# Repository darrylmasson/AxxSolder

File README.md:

Note - this is a fork of AxxSolder that replaces the MCU with the RP2040 because I felt like it. Major portions of this README will be rewritten at some point.

# AxxSolder Overview
AxxSolder is a STM32 based soldering iron controller for JBC C115, C210 and C245 cartridges. 
Two different versions are designed around the same PCB and software - one soldering station based on the [JBC ADS stand](https://www.jbctools.com/ad-sf-stand-for-t210-t245-handles-product-2018.html) and one portable version. The hardware takes a USB-C Power Delivery source. If a 65W, 20V USB-PD supply is used then NT115 and T210 handles can be powered at full power and T245 at limited power. The software is written for the RP2040 and implements a PID for temperature control, TFT display driver, sleep function when the handle is at rest and functions for read/write user settings to flash. Enclosures for both station and portable versions are 3D printed and design files are available under [/CAD](https://github.com/AxxAxx/AxxSolder/tree/main/CAD). A video showing the AxxSolder station can be found under [DEMO](#demo). A *bill of materials* (BOM) with individual component prices can be found under [/bom](https://github.com/AxxAxx/AxxSolder/tree/main/AxxSolder_hardware/bom).  

# Questions and support
Please use [Discord](https://discord.gg/dRD2ZfmyHY) for build related and general questions.

# Table of Contents
- [AxxSolder Overview](#axxsolder-overview)
- [Questions and support](#questions-and-support)
- [Features](#features)
- [Cartridge differences](#cartridge-differences)
- [Schematic](#schematic)
- [PCB](#pcb)
- [Software Version History and Hardware Compatibility](#software-version-history-and-hardware-compatibility)
- [DEMO](#demo)
- [AxxSolder Station](#axxsolder-station)
- [AxxSolder Portable](#axxsolder-portable)
- [Recommended power supply](#recommended-power-supply)
- [Handle identification and connections](#handle-identification-and-connections)
- [Firmware update](#firmware-update)
- [First start up after build](#first-start-up-after-build)
- [Settings](#settings)
- [PID control](#pid-control)
- [Temperature calibration](#temperature-calibration)
- [Temperature measurement](#temperature-measurement)

# Features
- The tip temperature is set by a rotary encoder. Pressing the encoder puts AxxSolder into Sleep mode and heating is turned off, press again to wake up.  
- AxxSolder is capable of driving C115, C210 and C245 style cartridges from JBC. With the "H_sense1" and "H_sense2" inputs AxxSolder can determine if the connected handle is either a NT115, T210 or T245 and adjust max output power accordingly. The max power output is limited in software to 120W for T245, 60W for T210 and 20W for NT115 handles.
- When the handle is put into the stand (connected to Stand_sense) AxxSolder goes into "Standby mode". On the portable version an aluminium plate is mounted and allows the AxxSolder to go into Standby mode when the cartridge or handle rests against it. After 10 min in Standby mode AxxSolder goes into "Sleep mode" and turns heating completely off. This is similar to what JBC calls [Sleep and Hibernation](https://www.jbctools.com/intelligent-heat-management.html).  
- If AxxSolder is left in normal running mode for longer than 30 min, the station automatically goes into sleep mode after 30 min as a safety feature.  
- Should the temperature ever go higher than 480 deg C overheating is detected and the station goes into sleep mode in order to protect the tip.
- User settings are stored in non volatile flash and can be configured via a settings menu described in [SETTINGS](#settings).
- The two buttons are used to store temperature presets, e.g. 330 deg C and 430 deg C. Both preset temperatures are configurable in the settings menu.
- The TFT display used in this project is a 2 inch 320x240 Color TFT display [2.0" 320x240 Color IPS TFT Display](https://www.adafruit.com/product/4311) and shows information about:
  - Set temperature
  - Actual temperature
  - Current power as a bar graph
  - In case of sleep mode, the power bar shows "ZzZzZz"
  - In case of Standby mode, the power bar shows "STANDBY"
  - Input voltage
  - MCU temperature
  - Current detected handle type

# Cartridge differences
Cartridges from JBC do all contain a thermocouple element to read the tip temperature and a resistive heater element. The configuration of thermocouple and heater element differ slightly between cartridge models. In order to determine the internal configuration of the cartridges two cross sections were done. These show clearly how the C210 and C245 cartridges are constructed internally. The images can be seen here: [https://www.eevblog.com/forum/projects/axxsolder-jbc-soldering-controller](https://www.eevblog.com/forum/projects/axxsolder-jbc-soldering-controller/msg5124267/#msg5124267).
As the thermocouple output also differs (see my measurements [Temperature calibration](#temperature-calibration)) the correct handle/cartridge type has to be set. This is done automatically be the inputs "Handle_sense_1" and "Handle_sense_2" This can be done thanks to the design of the handle connector. For the JCB T210 handle pin 5 and 6 are connected internally in the connector and for NT115 pin 3 and 5 should be connected. This allows AxxSolder to sense which handle is connected and assign correct thermocouple correction, PID parameters and max output power.

# Schematic
The schematic for AxxSolder is shown below. Both station and portable versions use the same PCB and software. The MCU is a [STM32G431CBT6](https://www.st.com/en/microcontrollers-microprocessors/stm32g431cb.html). 

# PCB
The PCBs are designed in KiCad and manufactured by [PCBWay](https://www.pcbway.com/). PCBWay has sponsored this project with PCBs and stencils. As usual the quality of the PCBs is great. As some components have a rather fine pitch (0,5 mm as of the LQFP-48 package of the STM32) and some packages are "no lead" with a bottom thermal pad e.g. the WSON-8 package of the OPA2387 it is suggested to use a stencil to apply solder paste and then reflow the board using either a reflow oven or hot-plate. The boards on the image below were reflowed on a hot-plate (a homemade AxxPlate). A microscope is also recommended and helpful during assembly.
Printed Circuit Boards with assembled components are shown in the image below.

A 3D view (from and back) of the AxxSolder PCB is generated with KiCad and shown below. 

# Software Version History and Hardware Compatibility
| Version | Date  | Hardware Compatibility |
|---------|------|----------------------|
|[v3.0.2](https://github.com/AxxAxx/AxxSolder/releases/tag/v3.0.1)|Apr 25, 2024|V3.*|
|[v3.0.1](https://github.com/AxxAxx/AxxSolder/releases/tag/v3.0.1)|Mar 26, 2024|V3.*|
|[v3.0.0](https://github.com/AxxAxx/AxxSolder/releases/tag/v3.0.0)|Mar 02, 2024|V3.*|
|[v2.2.4](https://github.com/AxxAxx/AxxSolder/releases/tag/v2.2.2)|Dec 11, 2023|V2.*|
|[v2.2.4](https://github.com/AxxAxx/AxxSolder/releases/tag/v2.2.2)|Nov 28, 2023|V2.*|
|[v2.2.3](https://github.com/AxxAxx/AxxSolder/releases/tag/v2.2.2)|Nov 25, 2023|V2.*|
|[v2.2.2](https://github.com/AxxAxx/AxxSolder/releases/tag/v2.2.2)|Oct 24, 2023|V2.*|
|[v2.2.0](https://github.com/AxxAxx/AxxSolder/releases/tag/v2.2.0)|Oct 20, 2023|V2.*|
|[v2.1.3-revC](https://github.com/AxxAxx/AxxSolder/releases/tag/v2.1.3-revC)|Oct 16, 2023|V2.*|
|[v2.1.1](https://github.com/AxxAxx/AxxSolder/releases/tag/v2.1.1)|Oct 7, 2023|V2.*|
|[v2.1.0](https://github.com/AxxAxx/AxxSolder/releases/tag/v2.1.0)|Oct 7, 2023|V2.*|

# DEMO
(This shows AxxSolder 2 and not the latest AxxSolder 3)  
Click on the gif to get to YouTube and see the demo in full resolution.  

# AxxSolder Station
The preferred setup is to pair AxxSolder with the [JBC ADS stand](https://www.jbctools.com/ad-sf-stand-for-t210-t245-handles-product-2018.html). This makes a very nice, compact and powerful soldering station. The JBC ADS stand is paired with a custom 3D printed enclosure for AxxSolder and the PCB is mounted with two mounting brackets. All 3D printed parts are available under [/CAD](https://github.com/AxxAxx/AxxSolder/tree/main/CAD). 
  
The JBC ADS stand comes with a silicone cable fitted with two Binder 99-0621-00-07 connectors. In order to use this cable a Binder 99-0624-00-07 is mounted into the AxxSolder enclosure and wired as the image below:  
  
By default, the stand separates the two signals coming from the "tool rest position" and the "tip change position" and does NOT have two separate connections for tip sensing 1 and 2 (as is needed). Therefore, a modification is done to the PCB inside the JBC ADS stand in order to combine the "tool rest position" and the "tip change position" sense into one connection and separate the two tip sense connections. This is shown in the image above. The stand is held together with two PH0 screws from the side. 

# AxxSolder Portable
It is often nice to have a compact and portable soldering iron controller for when you are away from your comfortable desk. A neat powerful package with the same capabilities as your main soldering station. This is why AxxSolder Portable was designed. The only difference between AxxSolder station and Portable is the enclosure. As AxxSolder accepts an input of 9-24 V it is compatible with a range of battery options. The author usually use a battery pack consisting of 12 Samsung INR18650 35E in a 3S4P configuration which works very well. The portable version has an aluminium tab on the enclosure connected to the same input on the PCB as the "handle rest" on the station version. This allows the user to rest the iron onto the aluminium tab and automatically enter sleep mode.   

The connections from the handle to the PCB through the Hirose RPC1-12RB-6P(71) connector is shown below. The blue wire in the portable version is connected to the aluminium plate which tells the AxxSolder to go into sleep mode when in contact with the soldering iron. The yellow wire is connected to pin 6 and is used to determine which handle is connected.

# Recommended power supply
A well-suited power supply with isolated output (SELV) is the Meanwell LRS-150-24. It is rated for 156 W at 24 V. A cover protecting the terminals for this power supply can be found under [/CAD](https://github.com/AxxAxx/AxxSolder/tree/main/CAD).  

# Handle identification and connections
In order for AxxSolder to know which type of handle (NT115, T210, T245) is connected specific pins must be connected within the handle connector. By default, the original JBC handle T245 has NO pins connected while in the original T210 pins 5 and 6 are connected. The original NT115 handle has a different connector from JBC and must be modified. If the user changes the connector or uses a non-genuine handle it is important to make sure that pin 5 and 3 is connected within the connector. All the necessary connections are shown in the image below. While powering on AxxSolder fir the first time after doing these connections within the handle connector or connections to AxxSolder it is wise to attach a handle without its cartridge and ensure that AxxSolder shows the correct handle type on the display. Failing to detect the handle type will cause damage to the tip as the thermal calibration and max power allowed will be wrong.  

# Firmware update
Programming or updating the firmware the STM32 MCU can be done in two ways, by using a SWD programmer or directly via USB. 
## SWD programmer
These come in a variety of models and are available from several different places online. In the below example a [STLINK-V3MINIE](https://www.st.com/en/development-tools/stlink-v3minie.html) SWD programmer is used. The MCU is programmed by the following steps:
1. Disconnect any soldering iron handles from AxxSolder during the firmware update process.
2. Download the latest AxxSolder.bin file from [Releases](https://github.com/AxxAxx/AxxSolder/releases)
3. Connect your SWD programmer to the target MCU with GND, 3.3V, (N)RST, SWCLK, SWDIO
4. If your SWD programmer *can not* supply 3.3V it is necessary to power the AxxSolder from an external supply.
5. Start your programming software. [STM32CubeProgrammer](https://www.st.com/en/development-tools/stm32cubeprog.html) is used in this example.
6. Connect to the target by selecting *ST-LINK* and click on *Connect*
7. Load the latest AxxSolder.bin downloaded in *Step 2* by clicking *Open file* and select the downloaded binary file.
8. Write the firmware to the MCU by clicking *Download*.
9. If you get the message *File download complete* everything succeeded and the SWD programmer can be disconnected and AxxSolder power cycled once and AxxSolder should boot.

## USB (DFU mode)
1. Disconnect any soldering iron handles from AxxSolder during the firmware update process.
2. Download the latest AxxSolder.bin file from [Releases](https://github.com/AxxAxx/AxxSolder/releases)
3. Connect AxxSolder via USB to a computer that runs [STM32CubeProgrammer](https://www.st.com/en/development-tools/stm32cubeprog.html).
4. Hold down the most right button while powering on AxxSolder to enter DFU mode.
5. Connect to the target by selecting *USB* and click on *Connect*
6. Load the latest AxxSolder.bin downloaded in *Step 2* by clicking *Open file* and select the downloaded binary file.
7. Write the firmware to the MCU by clicking *Download*.
8. If you get the message *File download complete* everything succeeded and the USB cable can be disconnected.
9. Power cycle once and AxxSolder should boot.

# First start up after build
The first start up after you have built your AxxSolder can be intense. Double check all solder connections under a loupe/microscope. Especially the OPA2387, LTC4440 and the STM32G431 are small packages with tight pad spacing and can have solder bridges. Do also double check the connections to the soldering iron/stand which are shown in this document under [AxxSolder Station](#axxsolder-station) and [AxxSolder Portable](#axxsolder-portable).  
The first thing to do after you have double-checked everything is to follow the steps under [Firmware update](#firmware-update). It is wise to do the first programming of AxxSolder without any handle piece and with only 3.3 V, not VDD. After the programming is done you can now power up AxxSolder again via either with 3.3 V, this time you can attach your handle. This allows you to test that your handle type is detected correctly (the detected handle type NT115/T210/T245 is shown in the display). The Standby feature can also be tested by touching the stand (STAND Input).  
If the handle is detected correctly, the Standby function works and the display works you proceed to test the 7.35V DC/DC. This is done by once again disconnect the handle, but this time apply current limited 9-24 V VDD. 100 mA at 24 V is enough to check that the display starts and that you can measure the 3 bus voltages; 3.3V, 7.35V and VDD. If the bus voltages look good and the display shows the main screen you are ready to apply full VDD power and attach the soldering handle.  
If you are not 110% sure about your soldering/connections it is wise to be on the safe side and keep your soldering tip in a water bath in over to prevent it from over-heating in an uncontrolled manner. During the development this method was used and saved a few of those expensive JBC cartridges..

# Settings
To access the user settings the user holds down the encoder button at start-up. A SETTINGS text is then presented and the button can be released. While in the settings there are several parameters available.
| Setting | Desciption  | Unit | Default |
|---------|------|----------------------|----------------------|
|Startup Temp|Default temperature selected after boot|deg C|330|
|Temp Offset|Temperature offset applied to measured temperature|deg C|0|
|Standby Temp|Temperature to go to after handle is set in stand|deg C|150|
|Standby Time|Time for which standby temperature is held before cooling down|minutes|10|
|Sleep Time|Time that the iron can be ON before cooling down (safety feature)|minutes|30|
|Buzzer Enable|Enable or Disable the buzzer|ON/OFF|ON|
|Preset Temp 1|Preset temperature for button 1|deg C|330|
|Preset Temp 2|Preset temperature for button 2|deg C|430|
|GPIO4 ON at run|Enable 3.3V output on GPIO4 when the iron is in run mode|ON/OFF|OFF|
|Screen rotation|Rotate the screen|"0"=-180 deg, "1"=-90 deg, "2"=0 deg, "3"=90 deg|2|
|Limit Power|Limit the output power|"0"=no user limit, "1"=10 W, "2"= 20 W, "3"= 30 W ...|0|
|-Load Default-|Load default parameters|N/A|N/A|
|-Save and Reboot-|Exit and Save|N/A|N/A|
|-Exit no Save-|Exit without Save|N/A|N/A|

# PID control
As the thermal mass of each cartridge differs the PID parameters should in theory be adjusted to each different cartridge. As a matter of simplification, the PID parameters are only different between the different handle types, NT115, T210 and T245. This gives a good enough PID performance in my tests. The Max allowed power is also different between handle types.
```c
	/* Determine if NT115 handle is detected */
	if((sensor_values.handle1_sense >= 0.5) && (sensor_values.handle2_sense < 0.5)){
		handle = NT115;
		sensor_values.max_power_watt = 20; //20W
		Kp = 3;
		Ki = 1;
		Kd = 0.25;
		PID_MAX_I_LIMIT = 100;
	}
	/* Determine if T210 handle is detected */
	else if((sensor_values.handle1_sense < 0.5) && (sensor_values.handle2_sense >= 0.5)){
		handle = T210;
		sensor_values.max_power_watt = 60; //60W
		Kp = 5;
		Ki = 5;
		Kd = 0.5;
		PID_MAX_I_LIMIT = 125;
	}
	else{
		handle = T245;
		sensor_values.max_power_watt = 120; //120W
		Kp = 8;
		Ki = 3;
		Kd = 0.5;
		PID_MAX_I_LIMIT = 150;
	}
	PID_SetTunings(&TPID, Kp, Ki, Kd); // Update PID parameters based on handle type
	PID_SetILimits(&TPID, -PID_MAX_I_LIMIT, PID_MAX_I_LIMIT); 	// Set max and min I limit
```
The PID parameters are adjusted to achieve a fast response with minimum overshoot and oscillation. The below image is showing the set temperature, actual temperature response as well as the P, I and D contributions during a heat-up cycle from 25 deg C to 330 deg C. This heat-up sequence takes ~1.5 seconds for a C210-007 cartridge.  

# Temperature calibration
The voltage from the thermocouple embedded inside the cartridge is amplified by an OPA2387 operational amplifier and then read by the ADC of the MCU. To correlate the measured ADC value to the cartridge temperature experiments were done. A constant power was applied to the heating element of the cartridge and the ADC value was read as well as the actual tip temperature. The tip temperature was measured by a "Soldering Tip Thermocouple" used in e.g. the Hakko FG-100.   
The measured data was recorded and plotted for both the C115, C210 and C245 cartridges. The specific cartridges used were the C115112, C210-007 and C245-945. The measured data were fitted to polynomial equations:  
$Temp_{C115}[deg] =  5.10e^{-5} * ADC^2 + 0.42* ADC + 20.15$  
$Temp_{C210}[deg] =  4.22e^{-6} * ADC^2 + 0.32* ADC + 20.97$  
$Temp_{C245}[deg] = -4.73e^{-7} * ADC^2 + 0.12* ADC + 23.78$  
These are then used in the software to retrieve correct tip temperatures.

# Temperature measurement
As the thermocouple and heater element is connected in series inside the JBC cartridges and the thermocouple voltage measures over the same pins as the heating element we have to be careful when to do the temperature measurement. In order to not disturb the thermocouple measurement with heater element switching, the switching is turned off for 0.5 ms just before the temperature measurement is taken. The 0.5 ms delay ensures that the switching is turned off and the thermocouple signal is stabilized around a stable voltage.  
The measured signal over the thermocouple is clamped to 3.3V with a BAV199 Schottky diode in order to protect the op-amp OPA2387. The voltage measurement is taken by the internal ADC in DMA mode with a circular buffer. The buffer holds several measurements which are averaged and filtered in software.  
The yellow curve in the image below (Channel 1) shows the PWM signal driving the gate of the MOSFET. The green curve shows the amplified voltage between GREEN and RED wire in the JBC handle for at 330 degree C and 5% power and the purple 25 degree C and at 80% power (the tip held under water trying to heat up).
The blue pulse indicates the wait time of 0.5 ms and the purple pulse is where the ADC is sampled.

# Current measurement
The current is sampled four times per second by a 30 us current pulse through the heater. This is done both to check if there is a functioning tip in the handle (otherwise the display shows "---" at current temp) and to be able to calculate the power drawn by the heater. By knowing how much the heater draws in ampere the actual power can be calculated by knowing the bus voltage and pulse duty cycle. to measure the current the gate to the MOSFET is turned on, 10 us later the voltage over the current shunt is sampled by the ADC and the result is converted. This is shown the image below.

## Stargazers over time

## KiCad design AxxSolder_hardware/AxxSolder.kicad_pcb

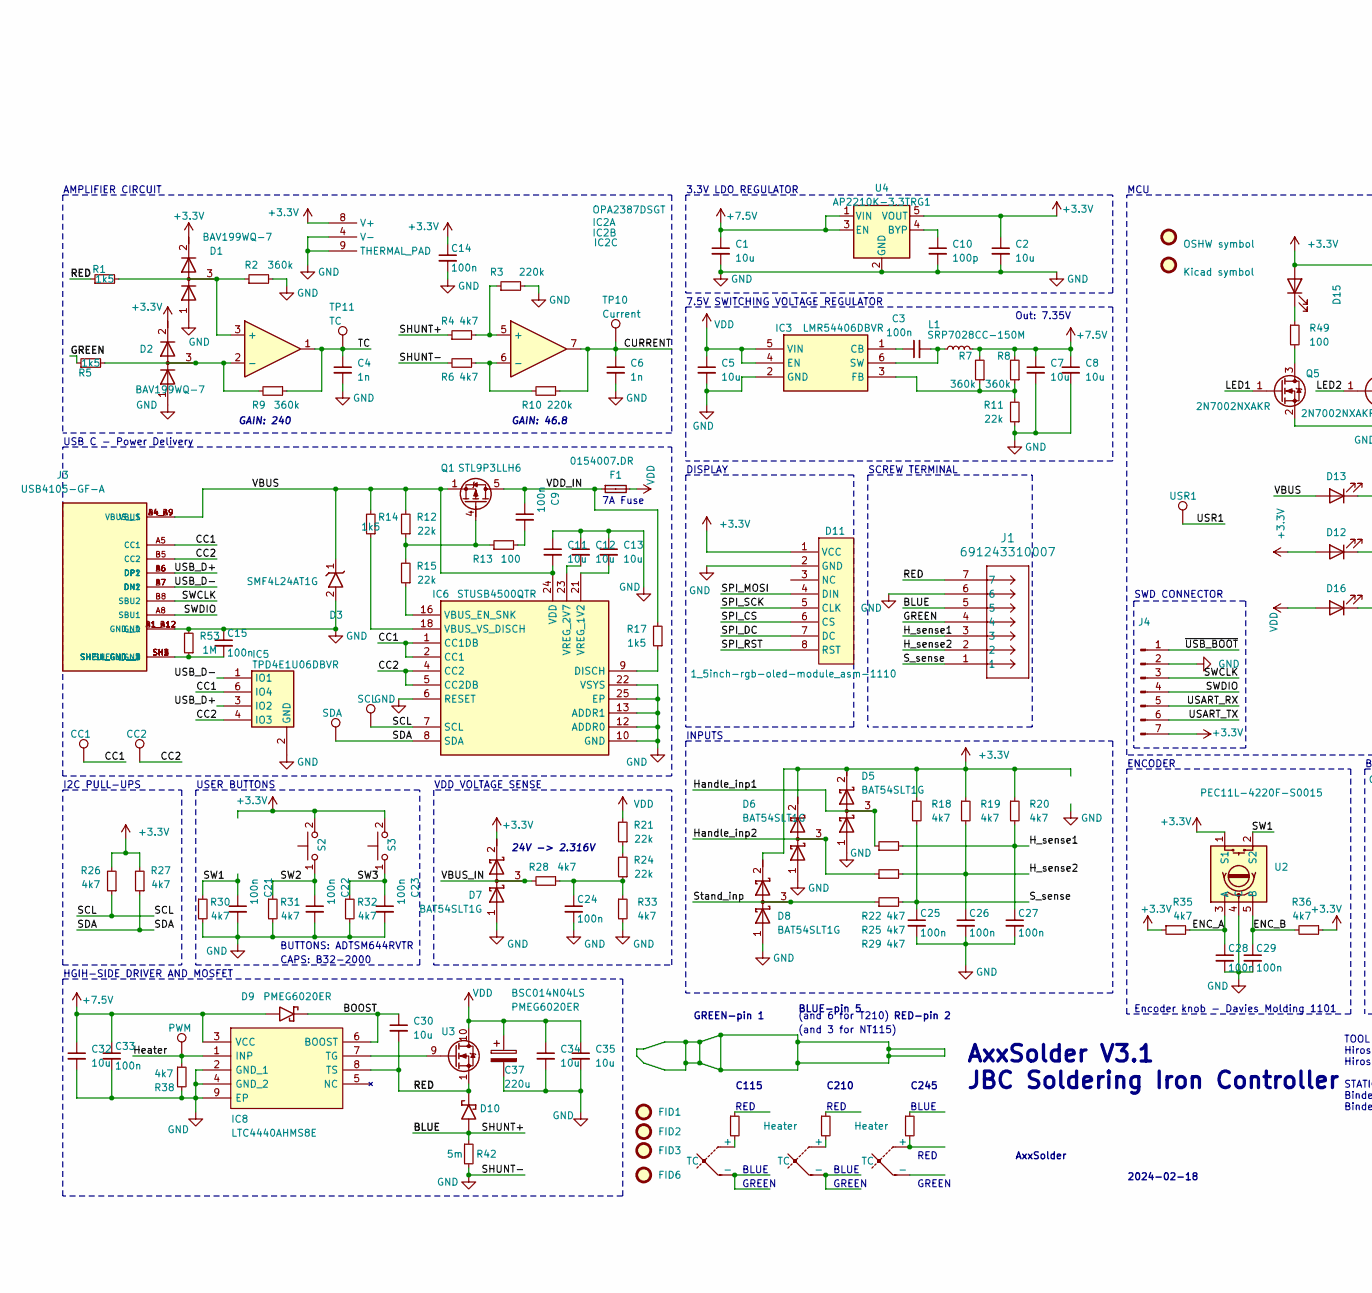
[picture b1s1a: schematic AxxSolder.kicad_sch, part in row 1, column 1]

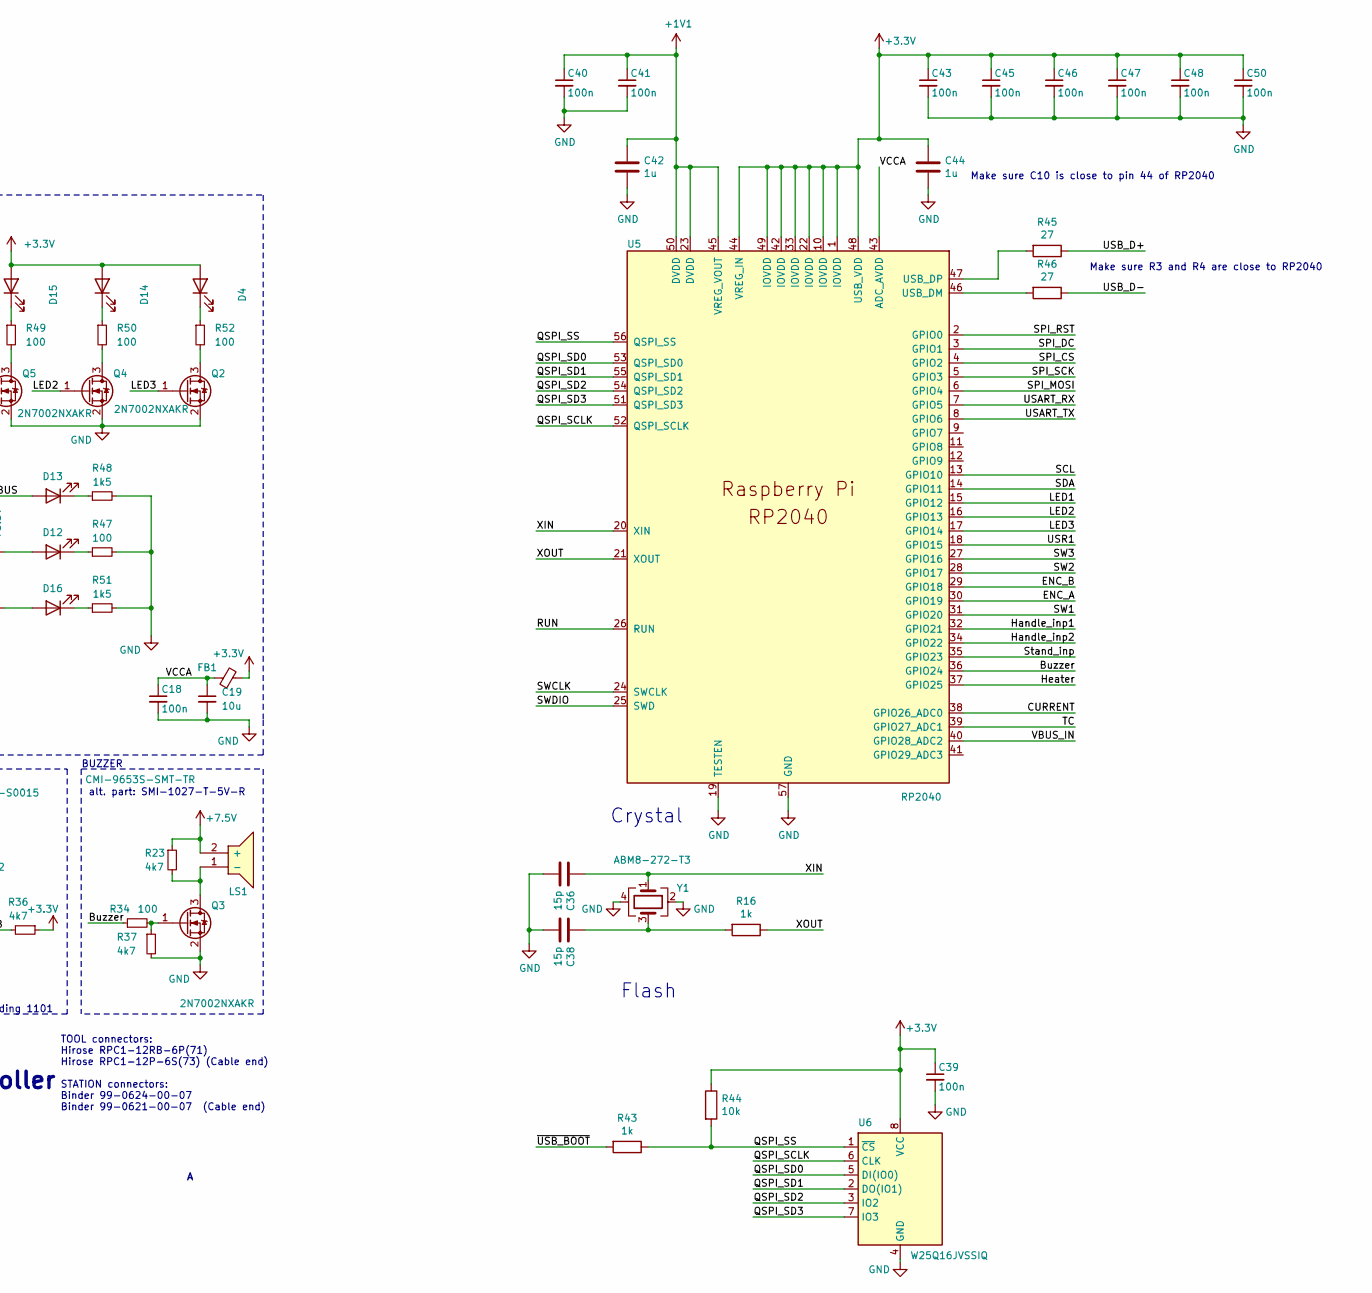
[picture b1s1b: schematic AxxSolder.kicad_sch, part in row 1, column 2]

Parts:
C1, C2, C5, C7, C8, C11, C12, C13, C19, C30, C32, C34, C35: 10u; C_0603_1608Metric; DigiKey PN 1276-1869-1-ND
C3, C9, C14, C15, C18, C21, C22, C23, C24, C25, C26, C27, C28, C29, C33, C39, C40, C41, C43, C45, C46, C47, C48, C50: 100n; C_0603_1608Metric; DigiKey PN 311-1341-1-ND
C4, C6: 1n; C_0603_1608Metric; DigiKey PN 399-C0603C102K3RAC7867CT-ND
C10: 100p; C_0603_1608Metric; DigiKey PN 1276-1908-1-ND
C36, C38: 15p; C_0603_1608Metric; DigiKey PN 311-1060-1-ND
C37: 220u; CAPAE830X1050N; DigiKey PN 399-6708-1-ND
C42, C44: 1u; C_0603_1608Metric; DigiKey PN 311-1445-1-ND
D1: BAV199WQ-7; SOT65P210X110-3N; Mouser Part Number 621-BAV199WQ-7
D2: BAV199WQ-7; SOT65P210X110-3N; DigiKey PN BAV199WQ-7DICT-ND
D3: SMF4L24AT1G; SODFL3619X98N; DigiKey PN 18-SMF4L24AT1GCT-ND
D4, D12, D13, D14, D15, D16: 150060VS75000; LED_0603_1608Metric; DigiKey PN 732-4980-1-ND
D5: BAT54SLT1G; SOT95P230X110-3N; DigiKey PN BAT54SLT1GOSCT-ND
D6, D7, D8: BAT54SLT1G; SOT95P230X110-3N; Manufacturer_Part_Number BAT54S; Mouser Part Number 637-BAT54S
D9: PMEG6020ER; PMEG6020ER115; DigiKey PN 1727-5217-1-ND
D10: PMEG6020ER; PMEG6020ER115; Mouser Part Number 771-PMEG6020ER-115
D11: 1_5inch-rgb-oled-module_asm-1110
F1: 0154007.DR; 0154100DR; DigiKey PN F1229CT-ND
FB1: BLM18HE601SN1D; R_0603_1608Metric; DigiKey PN 490-5214-1-ND
FID1, FID2, FID3, FID6: Fiducial; Fiducial_0.75mm_Mask1.5mm
FID4: OSHW symbol; OSHW-Logo_5.7x6mm_Copper
FID5: Kicad symbol; KiCad-Logo_6mm_SilkScreen
IC2: OPA2387DSGT; SON50P200X200X80-9N; DigiKey PN 296-OPA2387DSGTCT-ND
IC3: LMR54406DBVR; SOT95P280X145-6N; DigiKey PN 296-LMR54406DBVRCT-ND
IC5: TPD4E1U06DBVR; SOT95P280X145-6N; DigiKey PN TPD4E1U06DBVR
IC6: STUSB4500QTR; QFN50P400X400X100-25N-D; DigiKey PN 497-18060-1-ND
IC8: LTC4440AHMS8E; SOP65P490X110-9N; DigiKey PN 505-LTC4440AHMS8E-5#PBF-ND
J1: 691243310007; DigiKey PN 732-691243310007-ND
J3: USB4105-GF-A; GCT_USB4105-GF-A; DigiKey PN 2073-USB4105-GF-ACT-ND
J4: Conn_01x07_Pin; PinHeader_1x07_P2.54mm_Vertical
L1: SRP7028CC-150M; INDPM7366X300N; DigiKey PN 118-SRP7028CC-150MCT-ND
LS1: CMI-9653S-SMT-TR; CMI9653SSMTTR; DigiKey PN 102-3737-1-ND
Q1: STL9P3LLH6; STL20N6F7; DigiKey PN 497-17897-1-ND
Q2, Q3, Q4: 2N7002NXAKR; SOT95P230X110-3N; Manufacturer_Part_Number 2N7002NXAKR; Mouser Part Number 771-2N7002NXAKR
Q5: 2N7002NXAKR; SOT95P230X110-3N; DigiKey PN 2N7002NXAKR
R1, R5, R14, R17: 1k5; R_0603_1608Metric; Manufacturer_Part_Number ERJ-H3ED1501V; Mouser Part Number 667-ERJ-H3ED1501V
R2, R7, R8, R9: 360k; R_0603_1608Metric; Manufacturer_Part_Number ERJ-3RED3603V; Mouser Part Number 667-ERJ-3RED3603V
R3, R10: 220k; R_0603_1608Metric; Manufacturer_Part_Number ERJ-3RED2203V; Mouser Part Number 667-ERJ-3RED2203V
R4, R6, R18, R19, R20, R22, R23, R25, R26, R27, R28, R29, R30, R31, R32, R33, R35, R36, R37, R38: 4k7; R_0603_1608Metric; Manufacturer_Part_Number ERJ-3RBD4701V; Mouser Part Number 667-ERJ-3RBD4701V
R11, R12, R15, R21, R24: 22k; R_0603_1608Metric; Manufacturer_Part_Number ERJ-UP3J223V; Mouser Part Number 667-ERJ-UP3J223V
R13, R34: 100; R_0603_1608Metric; Manufacturer_Part_Number ERJ-P03F1000V; Mouser Part Number 667-ERJ-P03F1000V
R16, R43: 1k; R_0603_1608Metric; DigiKey PN 311-1.00KHRCT-ND
R39, R40: Heater
R41: Heater 2 OHM
R42: 5m; RESC6432X89N; DigiKey PN 541-10153-1-ND
R44: 10k; R_0603_1608Metric; DigiKey PN 311-10.0KHRCT-ND
R45, R46: 27; R_0603_1608Metric; DigiKey PN CR0603-FX-27R0ELFCT-ND
R47, R49, R50, R52: 100; R_0603_1608Metric; Manufacturer_Part_Number ERJ-3RBD4701V; Mouser Part Number 667-ERJ-3RBD4701V
R48, R51: 1k5; R_0603_1608Metric_Pad0.98x0.95mm_HandSolder; Manufacturer_Part_Number ERJ-3RBD4701V; Mouser Part Number 667-ERJ-3RBD4701V
R53: 1M; R_0603_1608Metric; Manufacturer_Part_Number ERJ-UP3J223V; Mouser Part Number 667-ERJ-UP3J223V
S2, S3: ADTSM644RVTR; DigiKey PN 679-ADTSM644RVTRCT-ND
TC1, TC2, TC3: TC
TP1: USR1; TestPoint_Pad_D1.0mm
TP7: CC1; TestPoint_Pad_D1.0mm
TP8: CC2; TestPoint_Pad_D1.0mm
TP10: Current; TestPoint_Pad_D1.0mm
TP11: TC; TestPoint_Pad_D1.0mm
TP15: SCL; TestPoint_Pad_D1.0mm
TP16: SDA; TestPoint_Pad_D1.0mm
TP17: PWM; TestPoint_Pad_D1.0mm
U2: PEC11L-4220F-S0015; PEC11L4220FS0015; DigiKey PN PEC11L-4220F-S0015-ND
U3: BSC014N04LS; DigiKey PN BSC014N04LSATMA1CT-ND
U4: AP2210K-3.3TRG1; SOT-23-5; DigiKey PN AP2210K-3.3TRG1DICT-ND
U5: RP2040; RP2040-QFN-56; DigiKey PN 2648-SC0914(13)CT-ND
U6: W25Q16JVSSIQ; SOIC-8_5.23x5.23mm_P1.27mm; DigiKey PN W25Q16JVSSIQ-ND
Y1: ABM8-272-T3; Crystal_SMD_3225-4Pin_3.2x2.5mm; DigiKey PN 535-ABM8-272-T3CT-ND

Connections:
+1V1: C40.1, C41.1, C42.1, U5.23 (DVDD), U5.45 (VREG_VOUT), U5.50 (DVDD)
+3.3V: C2.1, C14.1, C39.1, C43.1, C44.1, C45.1, C46.1, C47.1, C48.1, C50.1, D1.2, D2.2, D4.2 (A), D5.2 (K), D6.2 (K), D7.2 (K), D8.2 (K), D11.1 (VCC), D12.2 (A), D14.2 (A), D15.2 (A), FB1.2, IC2.8 (V+), J4.7, R18.1, R19.1, R20.1, R26.2, R27.2, R35.1, R36.1, R44.1, S2.2, S3.2, U2.1 (S1), U4.5 (VOUT), U5.1 (IOVDD), U5.10 (IOVDD), U5.22 (IOVDD), U5.33 (IOVDD), U5.42 (IOVDD), U5.44 (VREG_IN), U5.48 (USB_VDD), U5.49 (IOVDD), U6.8 (VCC)
+7.5V: C1.1, C7.1, C8.1, C32.1, C33.1, D9.2, IC8.3 (VCC), L1.2, LS1.2 (+), R7.2, R8.2, R23.1, U4.1 (VIN), U4.3 (EN)
/BLUE: D10.2, J1.5, R4.1, R42.1
/BOOST: C30.1, D9.1, IC8.6 (BOOST)
/Buzzer: R34.1, U5.36 (GPIO24)
/CC1: IC5.6 (IO4), IC6.1 (CC1DB), IC6.2 (CC1), J3.A5 (CC1), TP7.1
/CC2: IC5.4 (IO3), IC6.4 (CC2), IC6.5 (CC2DB), J3.B5 (CC2), TP8.1
/CURRENT: C6.1, IC2.7, R10.1, TP10.1, U5.38 (GPIO26_ADC0)
/ENC_A: C28.1, R35.2, U2.3 (A), U5.30 (GPIO19)
/ENC_B: C29.1, R36.2, U2.5 (B), U5.29 (GPIO18)
/GREEN: J1.4, R5.1
/H_sense1: C27.1, J1.3, R20.2, R22.2
/H_sense2: C26.1, J1.2, R19.2, R25.2
/Handle_inp1: D5.3 (common), R22.1, U5.32 (GPIO21)
/Handle_inp2: D6.3 (common), R25.1, U5.34 (GPIO22)
/Heater: IC8.1 (INP), R38.1, TP17.1, U5.37 (GPIO25)
/LED1: Q5.1 (G), U5.15 (GPIO12)
/LED2: Q4.1 (G), U5.16 (GPIO13)
/LED3: Q2.1 (G), U5.17 (GPIO14)
/QSPI_SCLK: U5.52 (QSPI_SCLK), U6.6 (CLK)
/QSPI_SD0: U5.53 (QSPI_SD0), U6.5 (DI(IO0))
/QSPI_SD1: U5.55 (QSPI_SD1), U6.2 (DO(IO1))
/QSPI_SD2: U5.54 (QSPI_SD2), U6.3 (IO2)
/QSPI_SD3: U5.51 (QSPI_SD3), U6.7 (IO3)
/QSPI_SS: R43.1, R44.2, U5.56 (QSPI_SS), U6.1 (~CS)
/RED: C30.2, D10.1, IC8.8 (TS), J1.7, R1.1, U3.1 (S)
/RUN: U5.26 (RUN)
/SCL: IC6.7 (SCL), R26.1, TP15.1, U5.13 (GPIO10)
/SDA: IC6.8 (SDA), R27.1, TP16.1, U5.14 (GPIO11)
/SPI_CS: D11.6 (CS), U5.4 (GPIO2)
/SPI_DC: D11.7 (DC), U5.3 (GPIO1)
/SPI_MOSI: D11.4 (DIN), U5.6 (GPIO4)
/SPI_RST: D11.8 (RST), U5.2 (GPIO0)
/SPI_SCK: D11.5 (CLK), U5.5 (GPIO3)
/SW1: C21.1, R30.1, U2.2 (S2), U5.31 (GPIO20)
/SW2: C22.1, R31.1, S2.1, U5.28 (GPIO17)
/SW3: C23.1, R32.1, S3.1, U5.27 (GPIO16)
/SWCLK: J3.B8 (SBU2), J4.3, U5.24 (SWCLK)
/SWDIO: J3.A8 (SBU1), J4.4, U5.25 (SWD)
/S_sense: C25.1, J1.1, R18.2, R29.2
/Stand_inp: D8.3 (common), R29.1, U5.35 (GPIO23)
/TC: C4.1, IC2.1, R9.1, TP11.1, U5.39 (GPIO27_ADC1)
/USART_RX: J4.5, U5.7 (GPIO5)
/USART_TX: J4.6, U5.8 (GPIO6)
/USB_D+: IC5.3 (IO2), J3.A6 (DP1), J3.B6 (DP2), R45.1
/USB_D-: IC5.1 (IO1), J3.A7 (DN1), J3.B7 (DN2), R46.1
/USR1: TP1.1, U5.18 (GPIO15)
/VBUS: C11.2, D3.1 (K), D13.2 (A), IC6.24 (VDD), J3.A4_B9 (VBUS), J3.B4_A9 (VBUS__1), Q1.1 (S), R12.2, R14.2
/VBUS_IN: D7.3 (common), R28.2, U5.40 (GPIO28_ADC2)
/VCCA: C18.1, C19.1, FB1.1, U5.43 (ADC_AVDD)
/VDD_IN: C9.1, F1.1, Q1.5 (D), R17.2
/XIN: C36.1, U5.20 (XIN), Y1.1
/XOUT: R16.1, U5.21 (XOUT)
/~USB_BOOT: J4.1, R43.2
GND: C1.2, C2.2, C4.2, C5.2, C6.2, C7.2, C8.2, C10.2, C11.1, C12.1, C13.1, C14.2, C15.1, C18.2, C19.2, C21.2, C22.2, C23.2, C24.2, C25.2, C26.2, C27.2, C28.2, C29.2, C32.2, C33.2, C34.2, C35.2, C36.2, C37.2, C38.2, C39.2, C40.2, C41.2, C42.2, C43.2, C44.2, C45.2, C46.2, C47.2, C48.2, C50.2, D1.1, D2.1, D3.2 (A), D5.1 (A), D6.1 (A), D7.1 (A), D8.1 (A), D11.2 (GND), IC2.4 (V-), IC2.9 (THERMAL_PAD), IC3.2 (GND), IC5.2 (GND), IC6.6 (RESET), IC6.10 (GND), IC6.12 (ADDR0), IC6.13 (ADDR1), IC6.22 (VSYS), IC6.25 (EP), IC8.2 (GND_1), IC8.4 (GND_2), IC8.9 (EP), J1.6, J3.A1_B12 (GND), J3.B1_A12 (GND__1), J4.2, Q2.2 (S), Q3.2 (S), Q4.2 (S), Q5.2 (S), R2.2, R3.2, R6.2, R11.1, R30.2, R31.2, R32.2, R33.2, R37.2, R38.2, R42.2, R47.2, R48.2, R51.2, R53.2, U2.4 (C), U4.2 (GND), U5.19 (TESTEN), U5.57 (GND), U6.4 (GND), Y1.2, Y1.4
unnamed: C9.2, R13.2
unnamed: C24.1, R24.1, R28.1, R33.1
unnamed: C38.1, R16.2, Y1.3
unnamed: D4.1 (K), R52.1
unnamed: D12.1 (K), R47.1
unnamed: D13.1 (K), R48.1
unnamed: D14.1 (K), R50.1
unnamed: D15.1 (K), R49.1
unnamed: D16.1 (K), R51.1
unnamed: D1.3, IC2.3 (+), R1.2, R2.1
unnamed: D2.3, IC2.2 (-), R5.2, R9.2
unnamed: IC2.5 (+), R3.1, R4.2
unnamed: IC2.6 (-), R6.1, R10.2
unnamed: C3.1, IC3.1 (CB)
unnamed: IC3.3 (FB), R7.1, R8.1, R11.2
unnamed: C3.2, IC3.6 (SW), L1.1
unnamed: IC6.9 (DISCH), R17.1
unnamed: IC6.16 (VBUS_EN_SNK), R15.1
unnamed: IC6.18 (VBUS_VS_DISCH), R14.1
unnamed: C13.2, IC6.21 (VREG_1V2)
unnamed: C12.2, IC6.23 (VREG_2V7)
unnamed: IC8.7 (TG), U3.9 (G)
unnamed: C15.2, J3.SH1 (SHELL_GND), J3.SH2 (SHELL_GND__1), J3.SH3 (SHELL_GND__2), J3.SH4 (SHELL_GND__3), R53.1
unnamed: LS1.1 (-), Q3.3 (D), R23.2
unnamed: Q1.4 (G), R12.1, R13.1, R15.2
unnamed: Q2.3 (D), R52.2
unnamed: Q3.1 (G), R34.2, R37.1
unnamed: Q4.3 (D), R50.2
unnamed: Q5.3 (D), R49.2
unnamed: R21.1, R24.2
unnamed: R39.2, TC1.1 (+)
unnamed: R40.2, TC2.1 (+)
unnamed: R41.2, TC3.1 (+)
unnamed: C10.1, U4.4 (BYP)
unnamed: R46.2, U5.46 (USB_DM)
unnamed: R45.2, U5.47 (USB_DP)
VDD: C5.1, C34.1, C35.1, C37.1, D16.2 (A), F1.2, IC3.4 (EN), IC3.5 (VIN), R21.2, U3.10 (D)

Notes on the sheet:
USER BUTTONS
C115
7A Fuse
Encoder knob - Davies Molding 1101
USB C - Power Delivery
BUTTONS: ADTSM644RVTR
Make sure R3 and R4 are close to RP2040
MCU
CAPS: B32-2000
Flash
GREEN
(and 3 for NT115)
GREEN-pin 1
RED
alt. part: SMI-1027-T-5V-R
(and 6 for T210)
SCREW TERMINAL
AMPLIFIER CIRCUIT
24V -> 2.316V
Crystal
VDD VOLTAGE SENSE
C245
ENCODER
SWD CONNECTOR
BLUE
BLUE-pin 5
2024-02-18
Make sure C10 is close to pin 44 of RP2040
BUZZER
7.5V SWITCHING VOLTAGE REGULATOR
AxxSolder V3.1 JBC Soldering Iron Controller
TOOL connectors: Hirose RPC1-12RB-6P(71) Hirose RPC1-12P-6S(73) (Cable end) STATION connectors: Binder 99-0624-00-07 Binder 99-0621-00-07 (Cable end)
C210
INPUTS
HGIH-SIDE DRIVER AND MOSFET
AxxSolder
RED-pin 2
RED
Out: 7.35V
I2C PULL-UPS

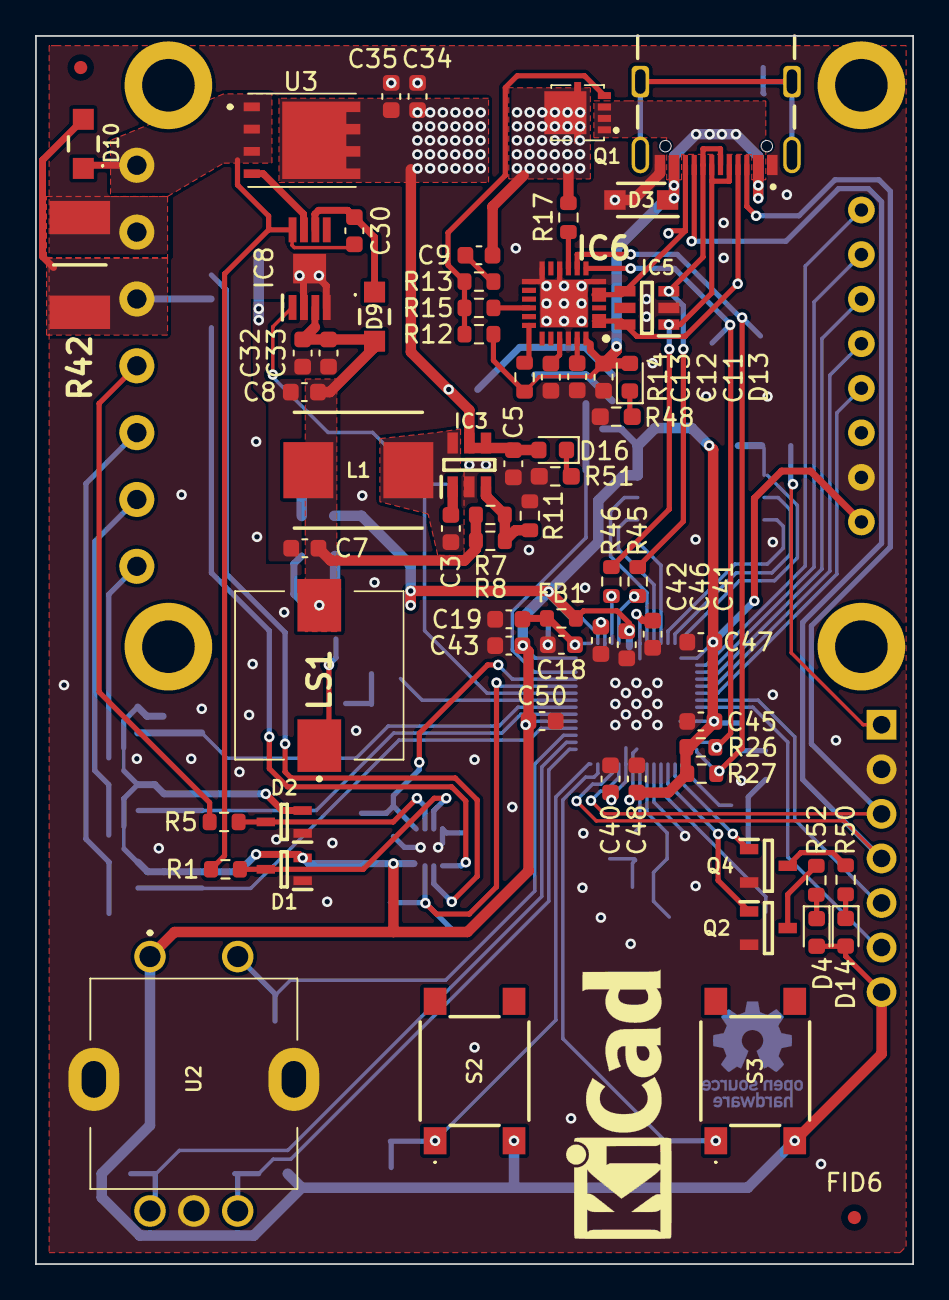
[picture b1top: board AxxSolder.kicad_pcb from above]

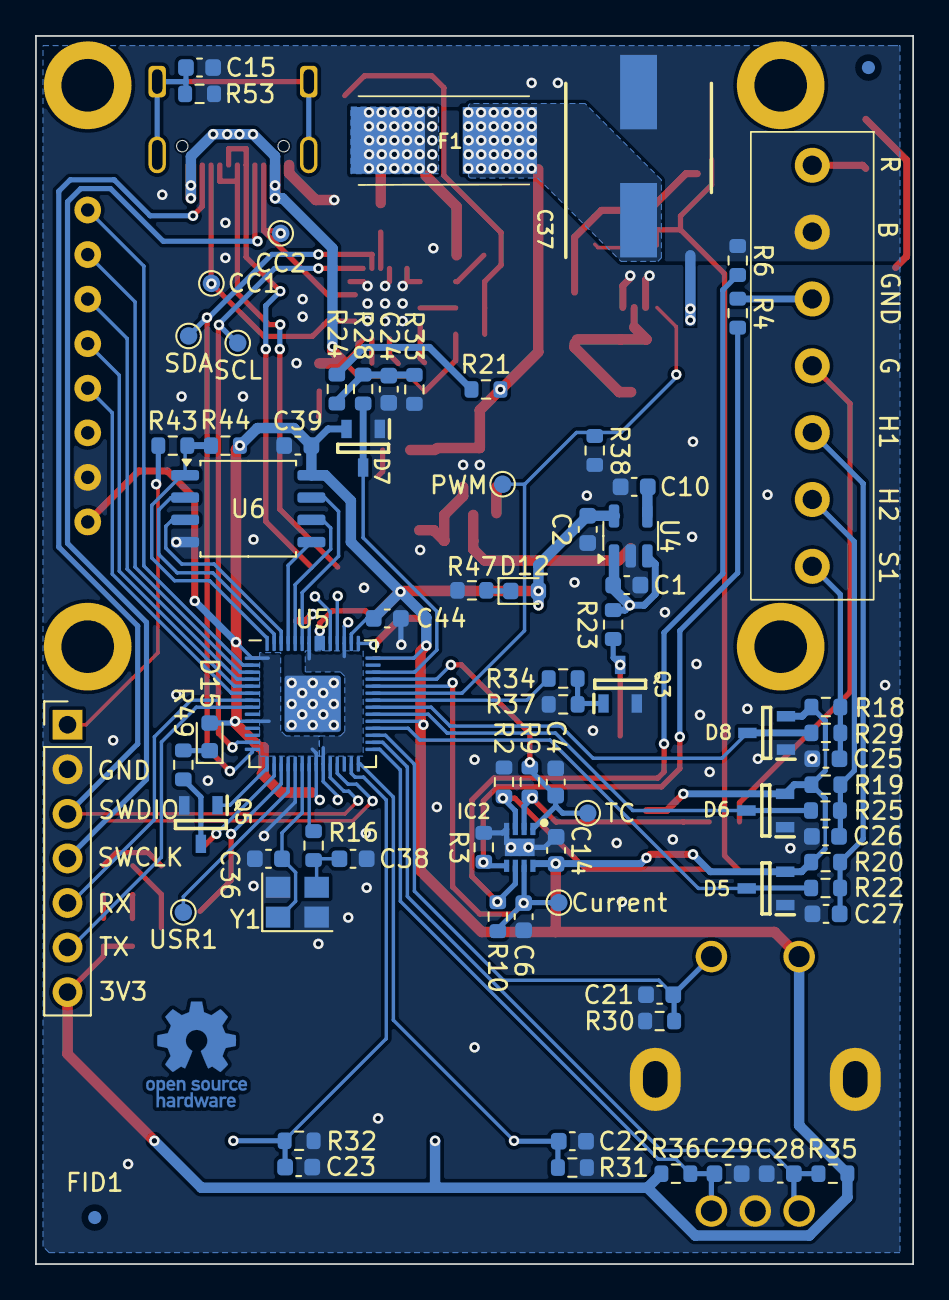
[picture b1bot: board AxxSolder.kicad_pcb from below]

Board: 2 copper layers, 50.0 x 70.0 mm, 150 parts (79 on the bottom side), 89 nets.

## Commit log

2024-05-20 Replace MCU with RP2040, new PCB layout
2024-05-25 Cleanup
2024-06-14 Ready?
2024-07-06 Best work yet
2024-07-07 Perfection
2024-07-19 Ordered this one

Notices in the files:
README.md:
License: GPL v3
